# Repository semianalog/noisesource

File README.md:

# Noise source, rev 1

Noise source for filter/amplifier testing, 1 MHz to 1 GHz. CC0/Public domain.

Consider rev 1 a work in progress; a second revision is needed before you can make this.

## Plots

Output: -30 dBm ± 2 dBm from 200 MHz to 1.2 GHz

Output: -25 dBm to -29 dBm from 1 MHz to 100 MHz

## Getting it

You probably don't want this revision. It has a bug: it oscillates around 1.6 GHz. A ferrite bead in the signal path damped this to the point where it's just a slight hump in the output spectrum (as seen above). I'm saving the existing Rev 1 PCBs, which require this modification, for distribution among friends on IRC. Rev 2 will have footprints for a few types of matching/damping circuits I plan to try between the noise diode and the first amplifier.

The PCB is designed to allow experimentation with different noise diodes. I built two variants. One shoves a lot of current through a [Panasonic DZ2410000L](http://www.semicon.panasonic.co.jp/ds4/DZ24100_E.pdf) 10V Zener diode, roughly along the lines of a Maxim application note presenting a similar circuit. Performance was quite poor. The second uses the emitter-base junction of an [MMBTH10](https://www.fairchildsemi.com/datasheets/MM/MMBTH10.pdf) RF transistor in reverse bias with a 1k source resistor, with much better performance. I recommend the latter.

## Assembly

Assembly is fairly obvious, just use the schematic as reference. For revision 2 I'll render a nice assembly diagram.

Revision 1 requires the insertion of a ferrite bead between DZ1 and C3. You'll have to cut the trace on the PCB and solder it in. I don't have a part number for the one I used, so this will require a bit of experimentation.

## Parts

Reference | Value | Manuf | MPN | Crit | Description
---|---|---|---|---|---
C1, C4 | 10µF | Murata | GRM319R6YA106KA12D | N | Power decoupling
C2, C3, C5, C6, C7, C8 | 68nF | Generic | 68nF 50V ≥X5R | N | RF {,de}coupling
DS1 | Blue | OSRAM | LB Q39G-L2OO-35-1 | N | Power LED
DZ1 | MMBTH10 | Fairchild | MMBTH10 | Y | Noise diode
E1, E2 | 150Ω at 100 MHz | Laird | LI1806C151R-10 | Y | RF filtering
J1 | +12V | Generic | 2-pin 100mil male header, unshrouded | N | Power input pins
J2 | SMA | TE Conn | 5-1814400-1 | N | RF output
MP1 | Shield | Laird | BMI-S-203-F and BMI-S-203-C | Y | RF shield
Q1 | PMOS | Vishay | SI2309CDS | N | Reverse polarity protector
R1 | 220kΩ | Generic | 220kΩ 5% 4x0603 (1206) | N | 4x 220k resistor network for general biasing
R2, R3 | 1Ω | Generic | 1Ω 5% 0603 | N | Damping impedance for C1, C4
R5 | 1kΩ | Generic | 1kΩ 5% 0603 | N | Noise diode bias resistor
U1 | 5V regulator | Fairchild | MC78M05CDTX | N | Regulator for MMICs
U2, U3 | RF amplifier | NXP | BGA2869 | Y | Main RF amplifiers

### Part selection comments

**DZ1:** The main noise diode. This is the most critical part in determining the output performance. The PCB is designed to let you experiment with different diodes, but to get the results I did, you should use an MMBTH10 transistor reverse-biased (emitter pin at DZ1 cathode pad, base pin at DZ1 anode pad).

**E1, E2:** Ferrite beads can be impressively poor under DC bias. If you must choose an alternative part for these, make sure to check the original datasheet for both impedance-vs-frequency and impedance-vs-DC-current and find something similar.

**U2, U3:** These are the main RF amplifiers and play a key role in determining performance. The original performance measurement was made with an NXP BGA2869. NXP has a line of similar amplifiers with the same pinout; if you're adventurous you could experiment with them.

**DS1:** I used a blue LED. A lot of people fuckin' *hate* blue LEDs. If you're one of them, pick a different LED here. Because blue LEDs are usually extremely efficient, you'll probably want to increase the driver current. R1 is used to set this current; select it to give the desired current when 12V-V<sub>F(LED)</sub> is applied across it. (The other three units of R1 are used as a voltage divider and their actual resistance doesn't matter; this is why R1 can be freely changed.)

**MP1:** The RF shield is listed as "critical" only because it is the only part number likely to fit the PCB footprint. If you manage to find another, go ahead and use it.

### Customizable bits

The power LED can be replaced with any color 0603 LED, if you hate blue. Different colors will require different bias currents; select R1 to provide the desired current.

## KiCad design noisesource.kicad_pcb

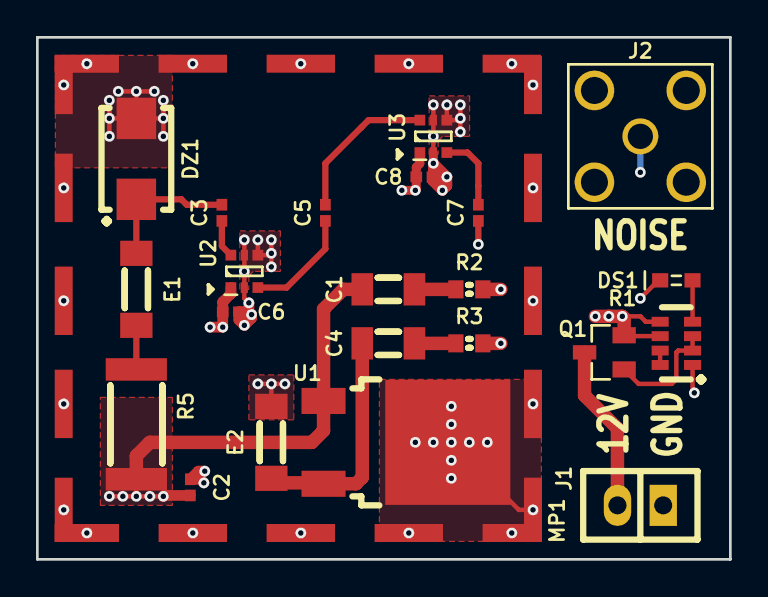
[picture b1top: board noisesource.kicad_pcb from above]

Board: 4 copper layers, 38.5 x 29.0 mm, 23 parts (0 on the bottom side), 17 nets.

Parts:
C1, C4: 10u; CAPC3216X70
C2, C3, C5, C6, C7, C8: 68n; CAPC1005X55
DS1: POWER; LED-0603
DZ1: 10V; DIOM5436X241
E1, E2: 150@100M; INDC4516X160
J1: POWER; CONN-100MIL-M-1x2
J2: OUT; CONN-CONSMA001
MP1: BMI-S-203; LAIRD-BMI-S-203
Q1: SI2309CDS; SOT-23
R1: 220k; RESCAXE80P160X320X70-8
R2, R3: 1R; RESC1608X50
R5: 33; RESC6432X70
U1: L78M05CDT; TO-252
U2, U3: BGA2869; SOT-363

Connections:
/+5: C4.1, E2.1, U1.2
/+5FILT: C6.2, C8.2, E2.2, U2.1, U3.1
/+12: C1.1, C2.2, Q1.2, R1.5, R1.6, R5.1, U1.1
GND: C2.1, C6.1, C8.1, DS1.1, DZ1.2, J1.1, J2.2, MP1.1, R1.1, R2.2, R3.2, U1.3, U2.2, U2.4, U2.5, U3.2, U3.4, U3.5
unnamed: C1.2, R2.1
unnamed: C3.1, U2.6
unnamed: C3.2, DZ1.1, E1.2
unnamed: C4.2, R3.1
unnamed: C5.1, U3.6
unnamed: C5.2, U2.3
unnamed: C7.1, J2.1
unnamed: C7.2, U3.3
unnamed: DS1.2, R1.4
unnamed: E1.1, R5.2
unnamed: J1.2, Q1.3
unnamed: Q1.1, R1.2, R1.3
unnamed: R1.7, R1.8

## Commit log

2016-04-14 Add renders
2016-04-14 Add README.md
2016-04-14 Adjust 3D link
2016-04-14 Add readme text
    Squashed commit of the following:
    commit 9443d55d747feb828c9e96cc61dfa3885e8419e1
    Author: Chris Pavlina <pavlina.chris@gmail.com>
    Date: Thu Apr 14 17:55:41 2016 -0400
    Update readme
    commit 256732c545369de18f6f24724a86526befcbd4f7

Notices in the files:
noisesource.kicad_pcb:
c4757p CC0 201604
